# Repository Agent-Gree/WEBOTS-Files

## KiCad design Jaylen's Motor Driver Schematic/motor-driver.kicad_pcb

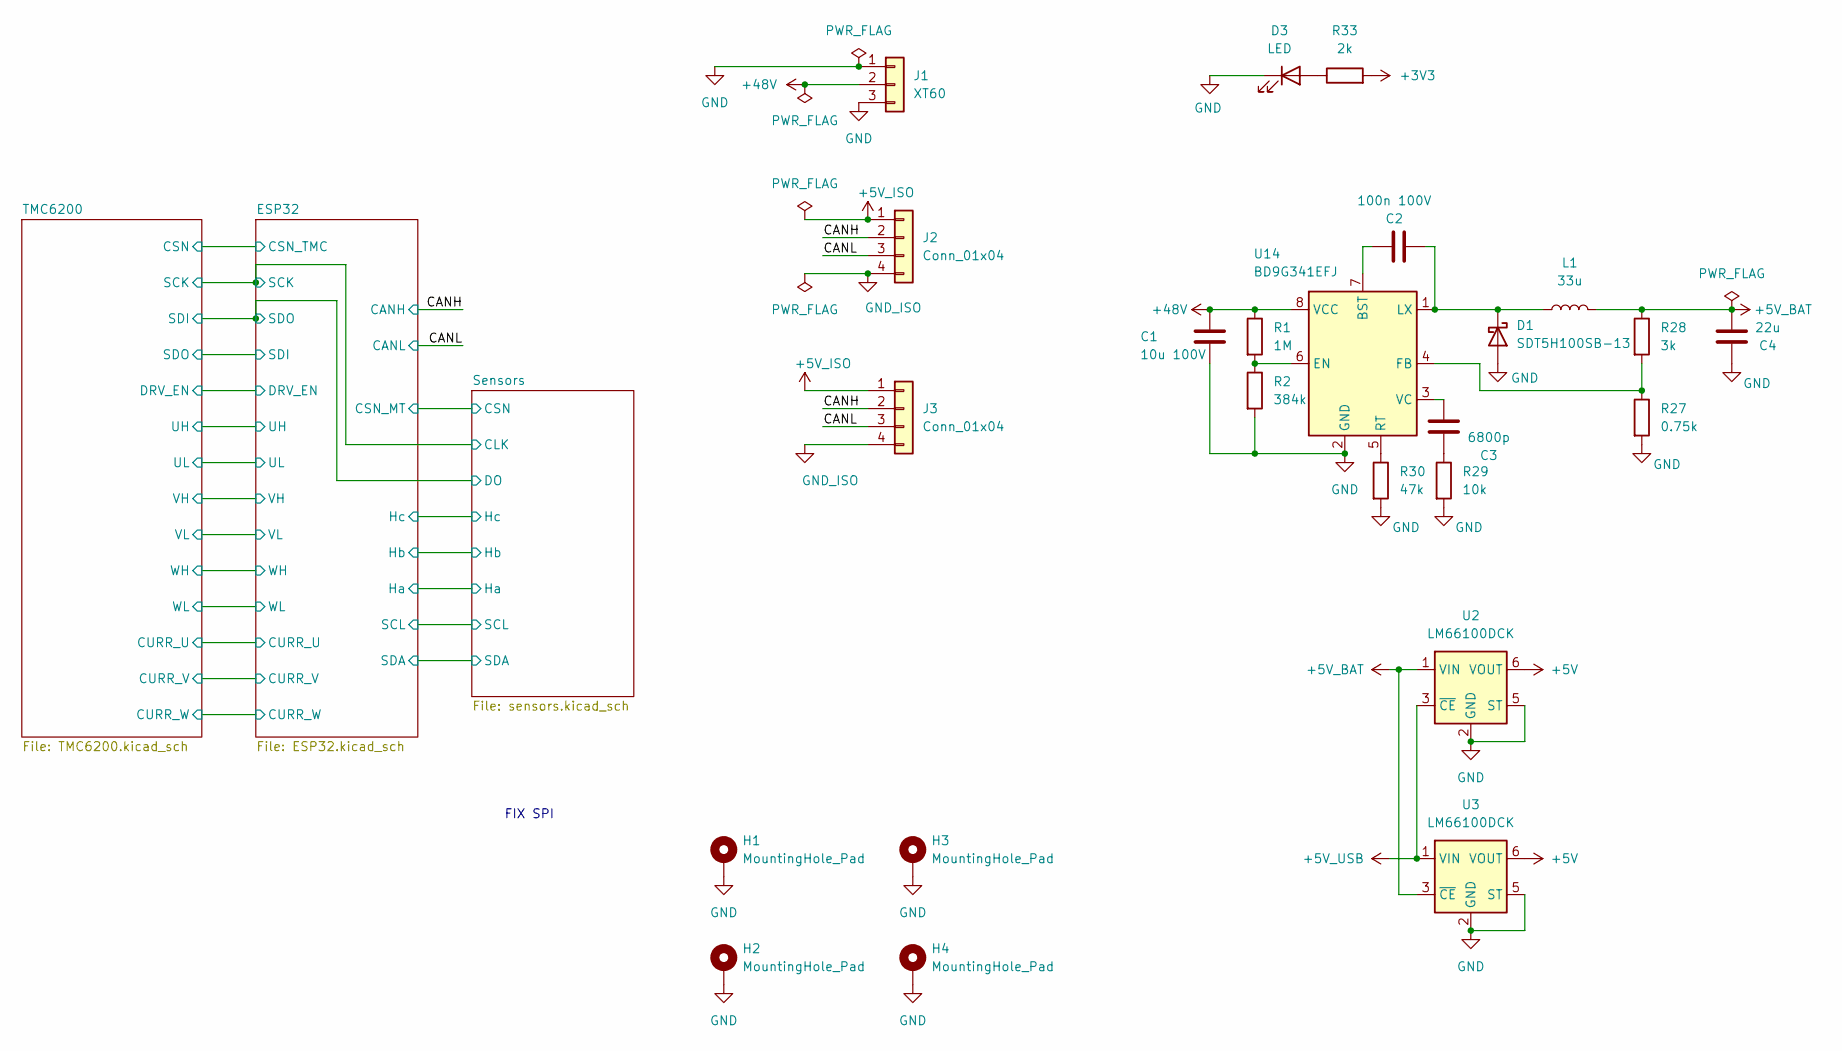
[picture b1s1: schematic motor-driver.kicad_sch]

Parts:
C1: 10u 100V; C_1210_3225Metric_Pad1.33x2.70mm_HandSolder
C2: 100n 100V; C_0805_2012Metric_Pad1.18x1.45mm_HandSolder; Voltage 100V; LCSC C28233
C3: 6800p; C_0805_2012Metric_Pad1.18x1.45mm_HandSolder; Voltage 100V; LCSC C28233
C4: 22u; C_0805_2012Metric_Pad1.18x1.45mm_HandSolder; LCSC C45783
D1: SDT5H100SB-13; D_SMB_Handsoldering
D3: LED; LED_0805_2012Metric_Pad1.15x1.40mm_HandSolder
H1, H2, H3, H4: MountingHole_Pad; MountingHole_2.7mm_M2.5_ISO14580_Pad_TopBottom
J1: XT60; AMASS_XT60IPW-M_1x03_P7.20mm_Horizontal
J2, J3: Conn_01x04; Molex_Micro-Fit_3.0_43045-0400_2x02_P3.00mm_Horizontal
L1: 33u; L_SXN_SMDRI127
R1: 1M; R_0603_1608Metric_Pad0.98x0.95mm_HandSolder; LCSC C22935
R2: 384k; R_0603_1608Metric_Pad0.98x0.95mm_HandSolder
R27: 0.75k; R_0603_1608Metric_Pad0.98x0.95mm_HandSolder
R28: 3k; R_0603_1608Metric_Pad0.98x0.95mm_HandSolder; LCSC C4211
R29: 10k; R_0603_1608Metric_Pad0.98x0.95mm_HandSolder; LCSC C25804
R30: 47k; R_0603_1608Metric_Pad0.98x0.95mm_HandSolder; LCSC C25819
R33: 2k; R_0603_1608Metric_Pad0.98x0.95mm_HandSolder; LCSC C22975
U2, U3: LM66100DCK; SOT-363_SC-70-6
U14: BD9G341EFJ; HTSOP-8-1EP_3.9x4.9mm_P1.27mm_EP2.4x3.2mm_ThermalVias

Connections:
+3V3: R33.2; also elsewhere on the board
+5V: U2.6 (VOUT), U3.6 (VOUT); also elsewhere on the board
+5V_BAT: C4.1, L1.2, R28.1, U2.1 (VIN), U3.3 (~CE)
+5V_ISO: J2.1, J3.1; also elsewhere on the board
+5V_USB: U2.3 (~CE), U3.1 (VIN); also elsewhere on the board
+48V: C1.1, J1.2, R1.1, U14.8 (VCC); also elsewhere on the board
/CANH: J2.2, J3.2; also elsewhere on the board
/CANL: J2.3, J3.3; also elsewhere on the board
GND: C1.2, C4.2, D1.2 (A), D3.1 (K), H1.1 (1_1), H2.1 (1_1), H3.1 (1_1), H4.1 (1_1), J1.1, J1.3, R2.2, R27.2, R29.2, R30.2, U2.2 (GND), U2.5 (ST), U3.2 (GND), U3.5 (ST), U14.2 (GND); also elsewhere on the board
GND_ISO: J2.4, J3.4; also elsewhere on the board
unnamed: C3.2, R29.1
unnamed: C2.1, D1.1 (K), L1.1, U14.1 (LX)
unnamed: D3.2 (A), R33.1
unnamed: C2.2, U14.7 (BST)
unnamed: R1.2, R2.1, U14.6 (EN)
unnamed: R27.1, R28.2, U14.4 (FB)
unnamed: R30.1, U14.5 (RT)
unnamed: C3.1, U14.3 (VC)

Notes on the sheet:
FIX SPI

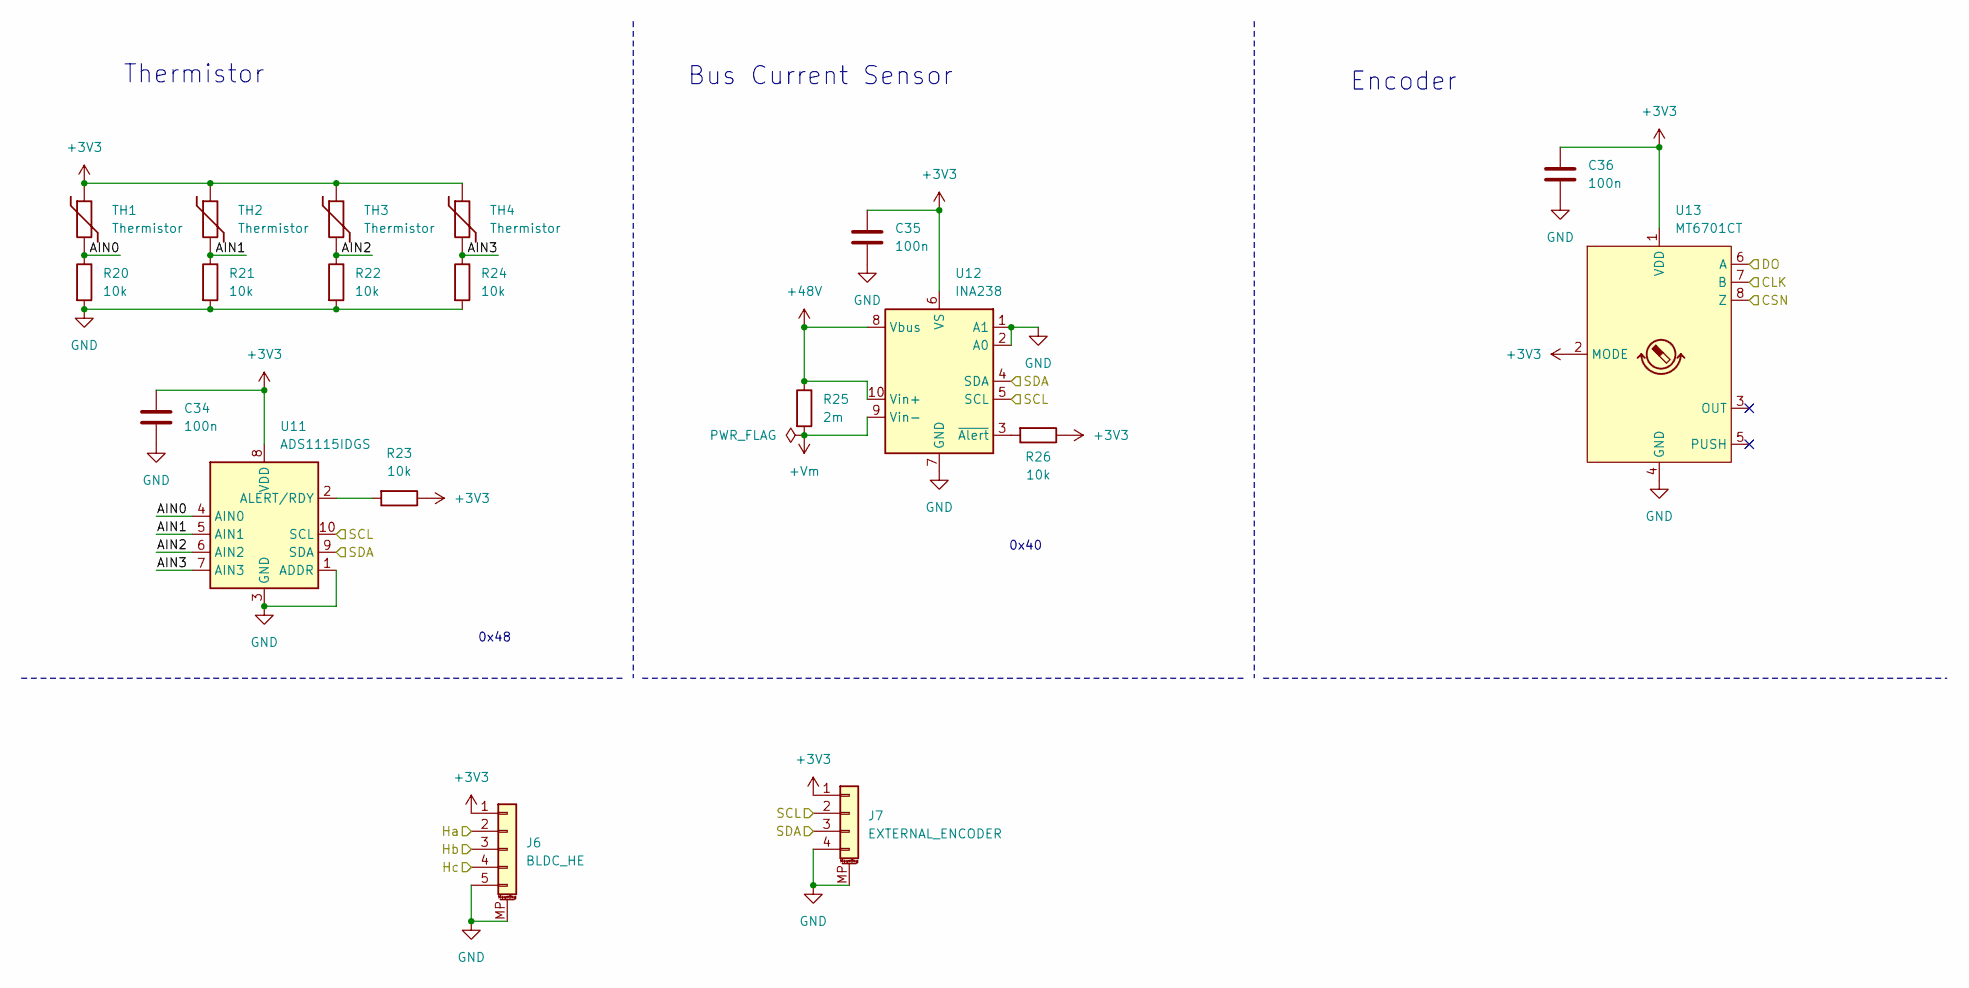
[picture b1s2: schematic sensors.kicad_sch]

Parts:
C34, C35, C36: 100n; C_0603_1608Metric_Pad1.08x0.95mm_HandSolder; LCSC C14663
J6: BLDC_HE; JST_GH_SM05B-GHS-TB_1x05-1MP_P1.25mm_Horizontal; LCSC C189891
J7: EXTERNAL_ENCODER; JST_GH_SM04B-GHS-TB_1x04-1MP_P1.25mm_Horizontal; LCSC C161692
R20, R21, R22, R23, R24, R26: 10k; R_0603_1608Metric_Pad0.98x0.95mm_HandSolder; LCSC C25804
R25: 2m; RES_3920R_1L00x_BRN-M
TH1, TH2: Thermistor; JST_GH_SM02B-GHS-TB_1x02-1MP_P1.25mm_Horizontal; LCSC C161690
TH3, TH4: Thermistor; R_0603_1608Metric_Pad0.98x0.95mm_HandSolder
U11: ADS1115IDGS; TSSOP-10_3x3mm_P0.5mm
U12: INA238; TSSOP-10_3x3mm_P0.5mm
U13: MT6701CT; SO-8_3.9x4.9mm_P1.27mm

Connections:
+3V3: C34.1, C35.1, C36.1, J6.1, J7.1, R23.1, R26.1, TH1.1, TH2.1, TH3.1, TH4.1, U11.8 (VDD), U12.6 (VS), U13.1 (VDD), U13.2 (MODE); also elsewhere on the board
+48V: R25.1, U12.8 (Vbus), U12.10 (Vin+); also elsewhere on the board
+Vm: R25.2, U12.9 (Vin-); also elsewhere on the board
/ESP32/CSN_MT: U13.8 (Z); also elsewhere on the board
/ESP32/Ha: J6.2; also elsewhere on the board
/ESP32/Hb: J6.3; also elsewhere on the board
/ESP32/Hc: J6.4; also elsewhere on the board
/ESP32/SCK: U13.7 (B); also elsewhere on the board
/ESP32/SCL: J7.2, U11.10 (SCL), U12.5 (SCL); also elsewhere on the board
/ESP32/SDA: J7.3, U11.9 (SDA), U12.4 (SDA); also elsewhere on the board
/ESP32/SDO: U13.6 (A); also elsewhere on the board
/Sensors/AIN0: R20.1, TH1.2, U11.4 (AIN0)
/Sensors/AIN1: R21.1, TH2.2, U11.5 (AIN1)
/Sensors/AIN2: R22.1, TH3.2, U11.6 (AIN2)
/Sensors/AIN3: R24.1, TH4.2, U11.7 (AIN3)
GND: C34.2, C35.2, C36.2, J6.5, J6.MP (MountPin), J7.4, J7.MP (MountPin), R20.2, R21.2, R22.2, R24.2, U11.1 (ADDR), U11.3 (GND), U12.1 (A1), U12.2 (A0), U12.7 (GND), U13.4 (GND); also elsewhere on the board
unnamed: R23.2, U11.2 (ALERT/RDY)
unnamed: R26.2, U12.3 (~Alert)

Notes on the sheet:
0x48
Bus Current Sensor
Thermistor
Encoder
0x40

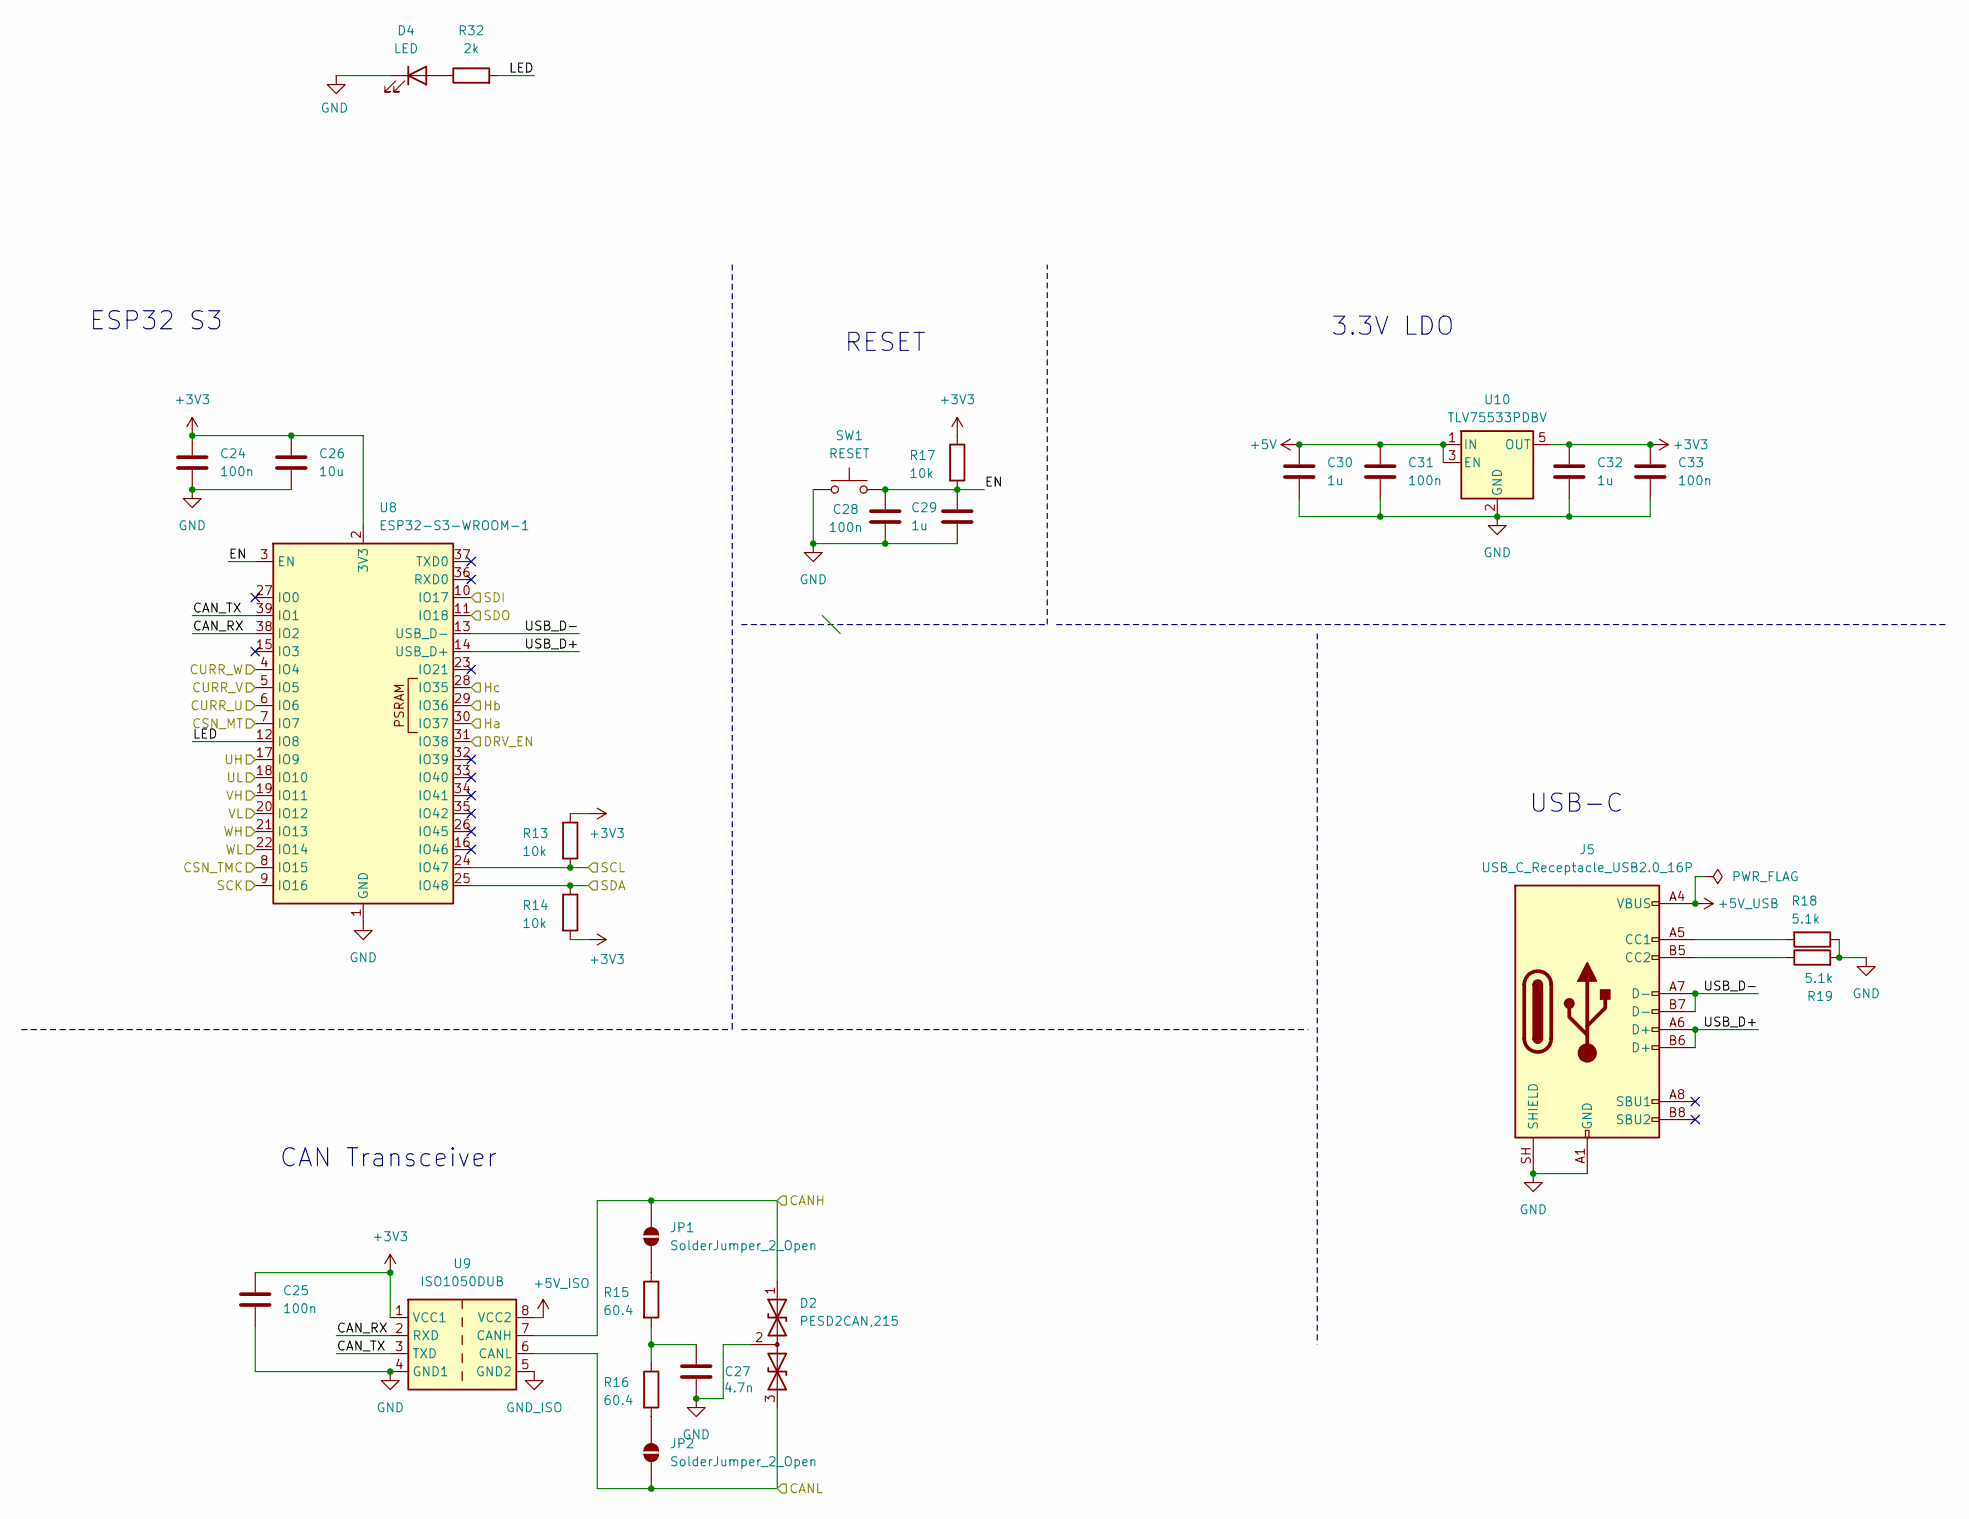
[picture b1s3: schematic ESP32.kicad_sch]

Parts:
C24, C25, C28, C31, C33: 100n; C_0603_1608Metric_Pad1.08x0.95mm_HandSolder; LCSC C14663
C26: 10u; C_0603_1608Metric_Pad1.08x0.95mm_HandSolder; LCSC C19702
C27: 4.7n; C_0603_1608Metric_Pad1.08x0.95mm_HandSolder; LCSC C53987
C29, C30, C32: 1u; C_0603_1608Metric_Pad1.08x0.95mm_HandSolder; LCSC C15849
D2: PESD2CAN,215; SOT-23_Handsoldering
D4: LED; LED_0805_2012Metric_Pad1.15x1.40mm_HandSolder
J5: USB_C_Receptacle_USB2.0_16P; better-SHOUHAN_TYPE-C_16PIN_2MD__073_; LCSC C2765186
JP1, JP2: SolderJumper_2_Open; SolderJumper-2_P1.3mm_Open_RoundedPad1.0x1.5mm
R13, R14, R17: 10k; R_0603_1608Metric_Pad0.98x0.95mm_HandSolder; LCSC C25804
R15, R16: 60.4; R_0603_1608Metric_Pad0.98x0.95mm_HandSolder
R18, R19: 5.1k; R_0603_1608Metric_Pad0.98x0.95mm_HandSolder; LCSC C23186
R32: 2k; R_0603_1608Metric_Pad0.98x0.95mm_HandSolder; LCSC C22975
SW1: RESET; SW_SPST_TS-1088-xR025
U8: ESP32-S3-WROOM-1
U9: ISO1050DUB; SOP-8_6.62x9.15mm_P2.54mm
U10: TLV75533PDBV; SOT-23-5

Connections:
+3V3: C24.1, C25.1, C26.1, C32.1, C33.1, R13.1, R14.2, R17.1, U8.2 (3V3), U9.1 (VCC1), U10.5 (OUT); also elsewhere on the board
+5V: C30.1, C31.1, U10.1 (IN), U10.3 (EN); also elsewhere on the board
+5V_ISO: U9.8 (VCC2); also elsewhere on the board
+5V_USB: J5.A4 (VBUS), J5.A9 (VBUS), J5.B4 (VBUS), J5.B9 (VBUS); also elsewhere on the board
/CANH: D2.1 (A1), JP1.2 (B), U9.7 (CANH); also elsewhere on the board
/CANL: D2.3 (A2), JP2.1 (A), U9.6 (CANL); also elsewhere on the board
/ESP32/CAN_RX: U8.38 (IO2), U9.2 (RXD)
/ESP32/CAN_TX: U8.39 (IO1), U9.3 (TXD)
/ESP32/CSN_MT: U8.7 (IO7); also elsewhere on the board
/ESP32/CSN_TMC: U8.8 (IO15); also elsewhere on the board
/ESP32/CURR_U: U8.6 (IO6); also elsewhere on the board
/ESP32/CURR_V: U8.5 (IO5); also elsewhere on the board
/ESP32/CURR_W: U8.4 (IO4); also elsewhere on the board
/ESP32/DRV_EN: U8.31 (IO38); also elsewhere on the board
/ESP32/EN: C28.2, C29.1, R17.2, SW1.2, U8.3 (EN)
/ESP32/Ha: U8.30 (IO37); also elsewhere on the board
/ESP32/Hb: U8.29 (IO36); also elsewhere on the board
/ESP32/Hc: U8.28 (IO35); also elsewhere on the board
/ESP32/LED: R32.2, U8.12 (IO8)
/ESP32/SCK: U8.9 (IO16); also elsewhere on the board
/ESP32/SCL: R13.2, U8.24 (IO47); also elsewhere on the board
/ESP32/SDA: R14.1, U8.25 (IO48); also elsewhere on the board
/ESP32/SDI: U8.10 (IO17); also elsewhere on the board
/ESP32/SDO: U8.11 (IO18); also elsewhere on the board
/ESP32/UH: U8.17 (IO9); also elsewhere on the board
/ESP32/UL: U8.18 (IO10); also elsewhere on the board
/ESP32/USB_D+: J5.A6 (D+), J5.B6 (D+), U8.14 (USB_D+)
/ESP32/USB_D-: J5.A7 (D-), J5.B7 (D-), U8.13 (USB_D-)
/ESP32/VH: U8.19 (IO11); also elsewhere on the board
/ESP32/VL: U8.20 (IO12); also elsewhere on the board
/ESP32/WH: U8.21 (IO13); also elsewhere on the board
/ESP32/WL: U8.22 (IO14); also elsewhere on the board
GND: C24.2, C25.2, C26.2, C27.2, C28.1, C29.2, C30.2, C31.2, C32.2, C33.2, D2.2 (common), D4.1 (K), J5.A1 (GND), J5.A12 (GND), J5.B1 (GND), J5.B12 (GND), J5.SH (SHIELD), R18.1, R19.2, SW1.1, U8.1 (GND), U8.40 (GND), U8.41 (GND), U9.4 (GND1), U10.2 (GND); also elsewhere on the board
GND_ISO: U9.5 (GND2); also elsewhere on the board
unnamed: C27.1, R15.2, R16.1
unnamed: D4.2 (A), R32.1
unnamed: J5.A5 (CC1), R18.2
unnamed: J5.B5 (CC2), R19.1
unnamed: JP1.1 (A), R15.1
unnamed: JP2.2 (B), R16.2

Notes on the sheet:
USB-C
ESP32 S3
CAN Transceiver
3.3V LDO
RESET

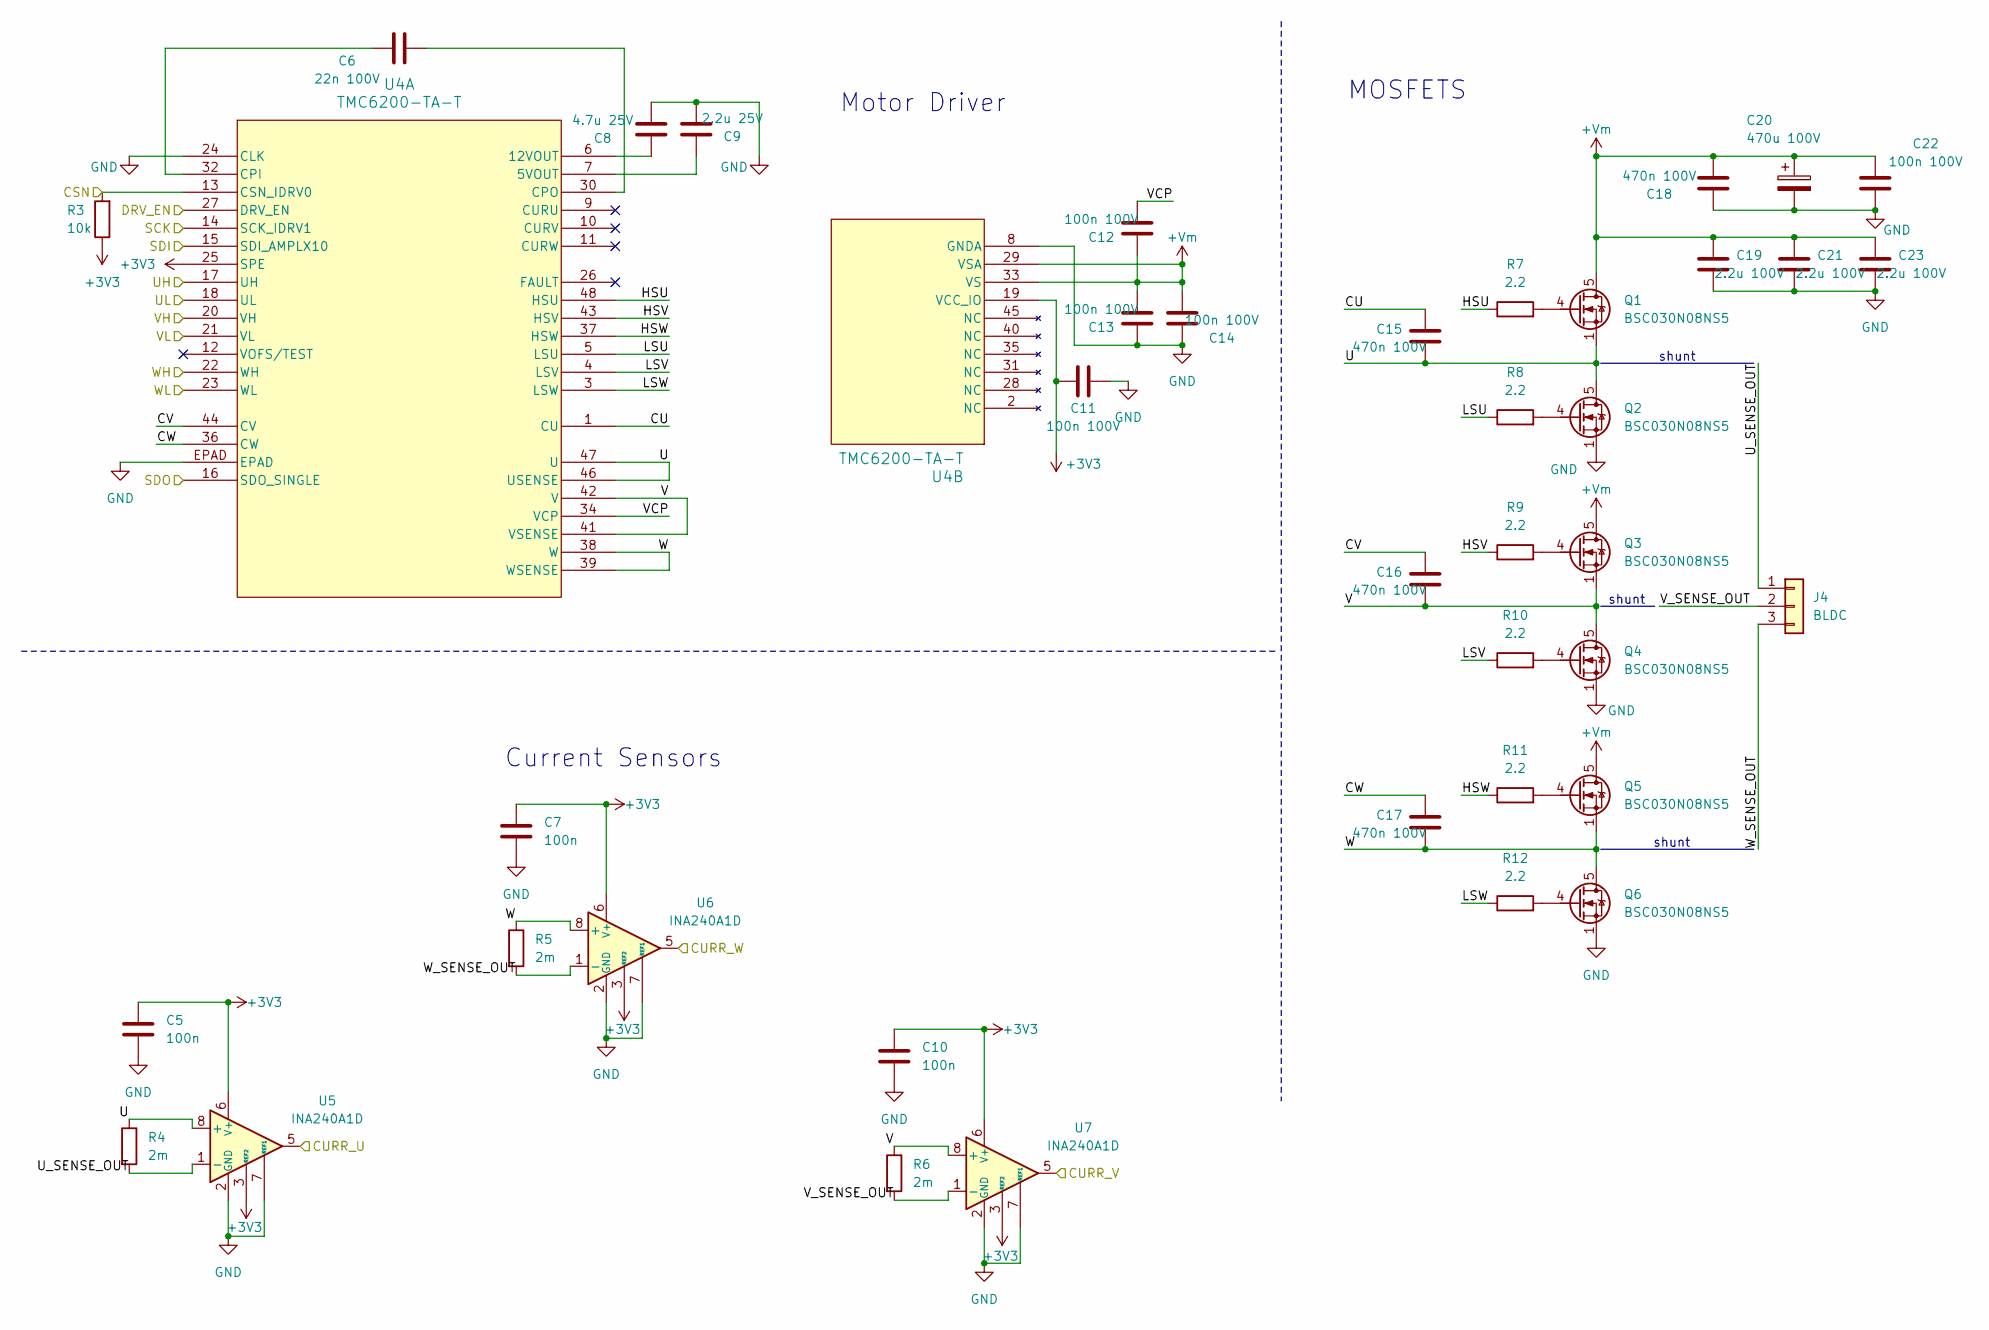
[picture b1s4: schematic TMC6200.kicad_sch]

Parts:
C5, C7, C10: 100n; C_0603_1608Metric_Pad1.08x0.95mm_HandSolder; LCSC C14663
C6: 22n 100V; C_0603_1608Metric_Pad1.08x0.95mm_HandSolder; Voltage 100V
C8: 4.7u 25V; C_0805_2012Metric_Pad1.18x1.45mm_HandSolder; Voltage 25V; LCSC C1779
C9: 2.2u 25V; C_0805_2012Metric_Pad1.18x1.45mm_HandSolder; Voltage 25V; LCSC C377773
C11, C12, C13, C14, C22: 100n 100V; C_0805_2012Metric_Pad1.18x1.45mm_HandSolder; Voltage 100V; LCSC C28233
C15, C16, C17, C18: 470n 100V; C_0805_2012Metric_Pad1.18x1.45mm_HandSolder; Voltage 100V
C19, C21, C23: 2.2u 100V; C_1206_3216Metric_Pad1.33x1.80mm_HandSolder; Voltage 100V
C20: 470u 100V; CP_Radial_D16.0mm_P7.50mm; Voltage 100V
J4: BLDC; SolderWire-2.5sqmm_1x03_P8.8mm_D2.4mm_OD4.4mm
Q1, Q2, Q3, Q4, Q5, Q6: BSC030N08NS5; TDSON-8-1
R3: 10k; R_0603_1608Metric_Pad0.98x0.95mm_HandSolder; LCSC C25804
R4, R5, R6: 2m; RES_3920R_1L00x_BRN-M
R7, R8, R9, R10, R11, R12: 2.2; R_0603_1608Metric_Pad0.98x0.95mm_HandSolder; LCSC C22939
U4: TMC6200-TA-T; eTQFP48_9x9_TRI; LCSC C915798
U5, U6, U7: INA240A1D; SOIC-8_3.9x4.9mm_P1.27mm

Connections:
+3V3: C5.1, C7.1, C10.1, C11.2, R3.1, U4.19 (VCC_IO), U4.25 (SPE), U5.3 (REF2), U5.6 (V+), U6.3 (REF2), U6.6 (V+), U7.3 (REF2), U7.6 (V+); also elsewhere on the board
+Vm: C12.1, C13.2, C14.2, C18.2, C19.1, C20.1, C21.1, C22.1, C23.1, Q1.5 (D), Q3.5 (D), Q5.5 (D), U4.29 (VSA), U4.33 (VS); also elsewhere on the board
/ESP32/CSN_TMC: R3.2, U4.13 (CSN_IDRV0); also elsewhere on the board
/ESP32/CURR_U: U5.5; also elsewhere on the board
/ESP32/CURR_V: U7.5; also elsewhere on the board
/ESP32/CURR_W: U6.5; also elsewhere on the board
/ESP32/DRV_EN: U4.27 (DRV_EN); also elsewhere on the board
/ESP32/SCK: U4.14 (SCK_IDRV1); also elsewhere on the board
/ESP32/SDI: U4.16 (SDO_SINGLE); also elsewhere on the board
/ESP32/SDO: U4.15 (SDI_AMPLX10); also elsewhere on the board
/ESP32/UH: U4.17 (UH); also elsewhere on the board
/ESP32/UL: U4.18 (UL); also elsewhere on the board
/ESP32/VH: U4.20 (VH); also elsewhere on the board
/ESP32/VL: U4.21 (VL); also elsewhere on the board
/ESP32/WH: U4.22 (WH); also elsewhere on the board
/ESP32/WL: U4.23 (WL); also elsewhere on the board
/TMC6200/CU: C15.2, U4.1 (CU)
/TMC6200/CV: C16.2, U4.44 (CV)
/TMC6200/CW: C17.2, U4.36 (CW)
/TMC6200/HSU: R7.1, U4.48 (HSU)
/TMC6200/HSV: R9.1, U4.43 (HSV)
/TMC6200/HSW: R11.1, U4.37 (HSW)
/TMC6200/LSU: R8.1, U4.5 (LSU)
/TMC6200/LSV: R10.1, U4.4 (LSV)
/TMC6200/LSW: R12.1, U4.3 (LSW)
/TMC6200/U: C15.1, Q1.1 (S), Q1.2 (S), Q1.3 (S), Q2.5 (D), R4.1, U4.46 (USENSE), U4.47 (U), U5.8 (+)
/TMC6200/U_SENSE_OUT: J4.1, R4.2, U5.1 (-)
/TMC6200/V: C16.1, Q3.1 (S), Q3.2 (S), Q3.3 (S), Q4.5 (D), R6.1, U4.41 (VSENSE), U4.42 (V), U7.8 (+)
/TMC6200/VCP: C12.2, U4.34 (VCP)
/TMC6200/V_SENSE_OUT: J4.2, R6.2, U7.1 (-)
/TMC6200/W: C17.1, Q5.1 (S), Q5.2 (S), Q5.3 (S), Q6.5 (D), R5.1, U4.38 (W), U4.39 (WSENSE), U6.8 (+)
/TMC6200/W_SENSE_OUT: J4.3, R5.2, U6.1 (-)
GND: C5.2, C7.2, C8.2, C9.1, C10.2, C11.1, C13.1, C14.1, C18.1, C19.2, C20.2, C21.2, C22.2, C23.2, Q2.1 (S), Q2.2 (S), Q2.3 (S), Q4.1 (S), Q4.2 (S), Q4.3 (S), Q6.1 (S), Q6.2 (S), Q6.3 (S), U4.8 (GNDA), U4.24 (CLK), U4.EPAD, U5.2 (GND), U5.4 (GND), U5.7 (REF1), U6.2 (GND), U6.4 (GND), U6.7 (REF1), U7.2 (GND), U7.4 (GND), U7.7 (REF1); also elsewhere on the board
unnamed: Q1.4 (G), R7.2
unnamed: Q2.4 (G), R8.2
unnamed: Q3.4 (G), R9.2
unnamed: Q4.4 (G), R10.2
unnamed: Q5.4 (G), R11.2
unnamed: Q6.4 (G), R12.2
unnamed: C9.2, U4.7 (5VOUT)
unnamed: C8.1, U4.6 (12VOUT)
unnamed: C6.1, U4.32 (CPI)
unnamed: C6.2, U4.30 (CPO)

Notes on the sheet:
shunt
Current Sensors
Motor Driver
MOSFETS

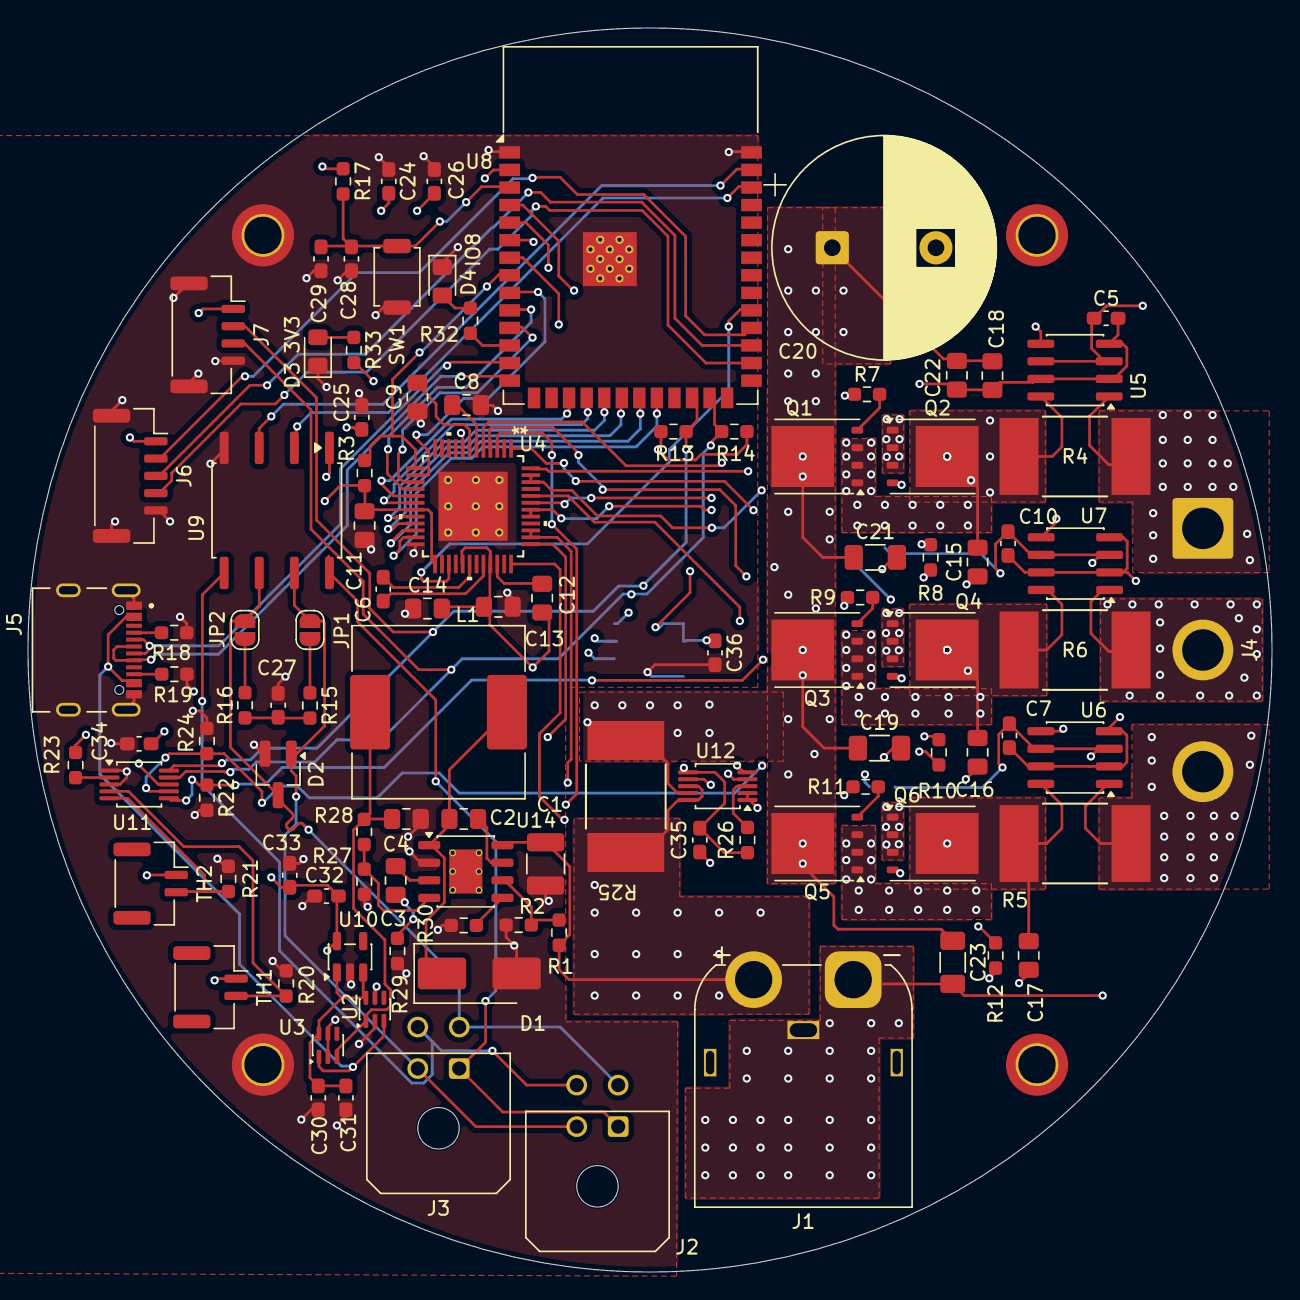
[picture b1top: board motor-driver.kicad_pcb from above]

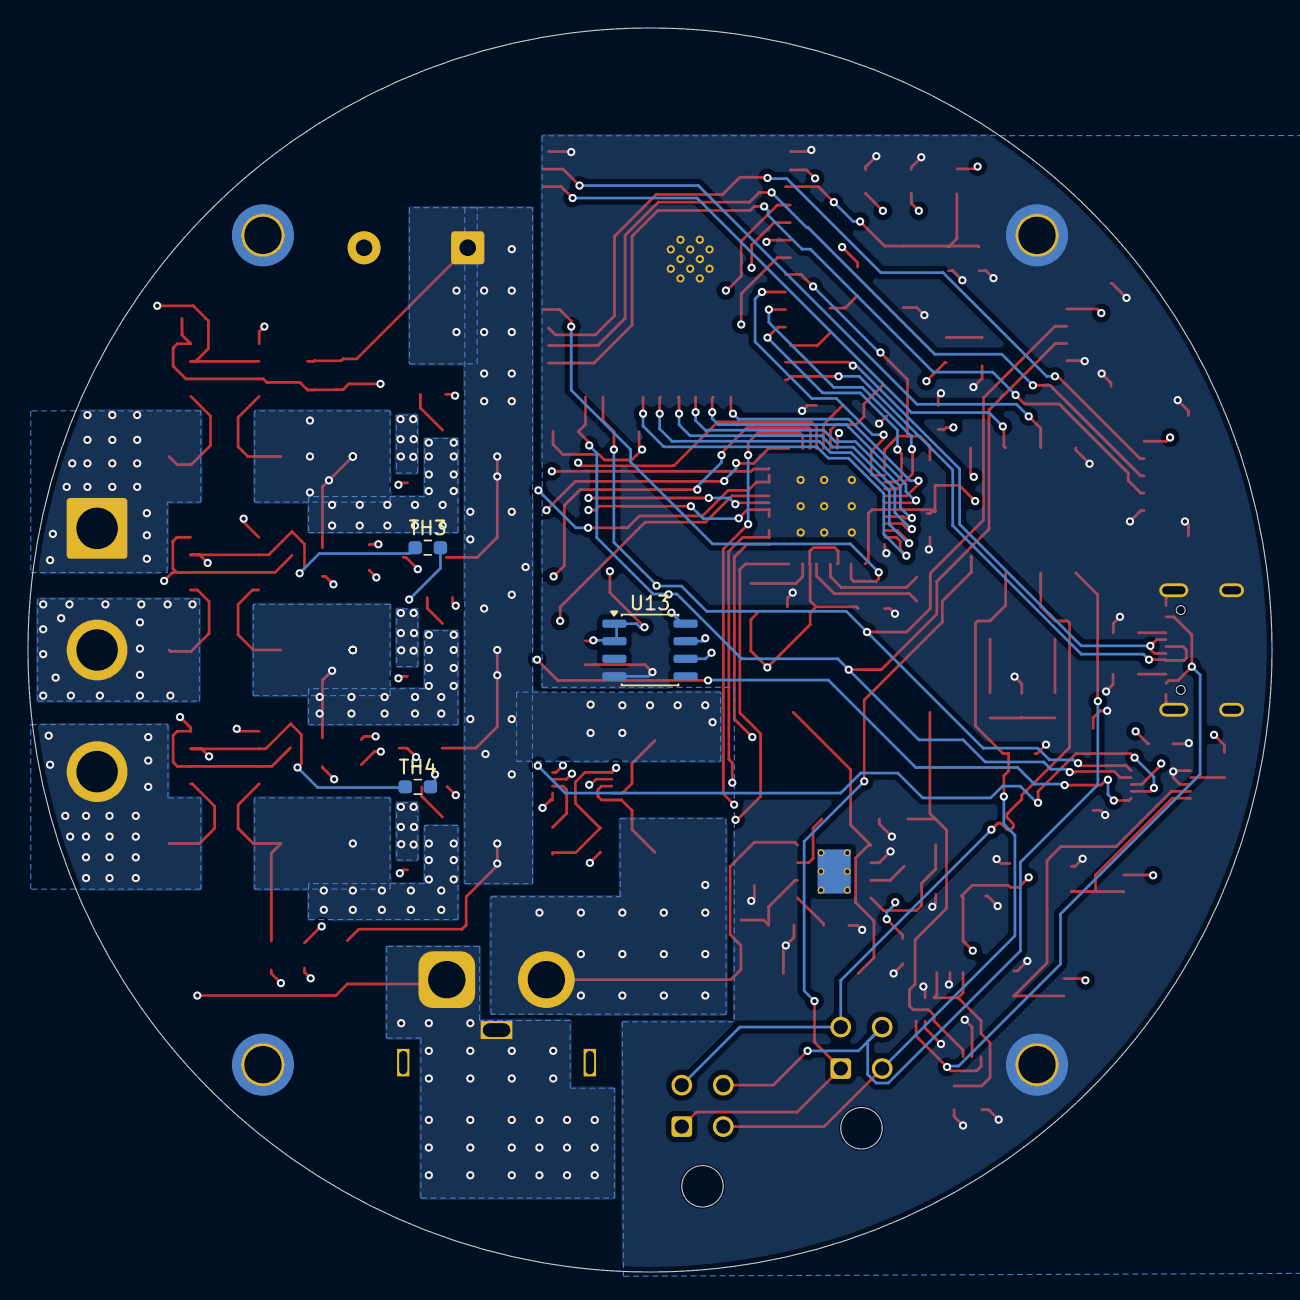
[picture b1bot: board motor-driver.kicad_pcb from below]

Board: 4 copper layers, 90.0 x 90.0 mm, 110 parts (3 on the bottom side), 83 nets.

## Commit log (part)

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2026-02-19 Copied all original WEBOTS files on personal computer
2026-02-19 Added a comment on Eugene's old code to test pushing to main
2026-02-27 Added a space
2026-02-27 Changed printf to Serial.printf Changed the tx_frame.data from [1] to [0].
2026-03-11 Changed parameters for receiver to match SPARKMAX specifications
2026-03-13 Added comments to remember to add the ability to read current, voltage, position, and position
2026-03-20 Changed baud rate to match serial monitor, changed CAN to be able to read extended CAN frames, and added documentation to track progress.
2026-04-03 Modified receiver and transmitter codes so they can communicate.
2026-05-17 Create a .dbc file to define the CAN message structure
2026-05-17 Added template codes and started my own codes (The Brain and The Motor Controller)
2026-05-17 Organized folders to include the header file in both "brain" ESP32 and "motor controller (mc)" ESP32. Began copying Claude's template to my own file ("The Brain") so that I can understand how it work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
2026-05-19 Copied code to personal file and have understood it. Added header file to personal code project folders (for Brain and Motor Controller)
2026-05-19 Added notes on what to do next
2026-05-23 Added new IDs, byte values, etc. for PID control to header files To do: Add code from Claude to add abilty to set rpm and position, to read voltage, position, and PID values To do: Hand-write new cod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
2026-05-27 Updated header file with stuff for PID, setting rpm and position Added PID control loop to set rpm and position Added function (placeholder) to set rpm (maybe via analogWrite to some pin on the ESP32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
2026-06-04 Fixed bugs in both Brain and Motor Controller codes Verified both codes. Success!
2026-06-05 Fixed all compile errors (both codes run without compilation errors)
2026-06-06 Changed all message IDs to be 29-bit extended frame The MCP2515 library was ORing the ID with a flag bit to indicate it's a 29-bit frame, so it was reading a different value than expected and not res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
2026-06-06 Made function to request motor telemetry Can now request and receive motor telemetry Tested setting the rpm and position ALL WORK! Thank GOD! To do: Figure out how to home the position (zero the enco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
2026-06-10 Requested something different from the motor controller (for the demo sent to Jaylen)
